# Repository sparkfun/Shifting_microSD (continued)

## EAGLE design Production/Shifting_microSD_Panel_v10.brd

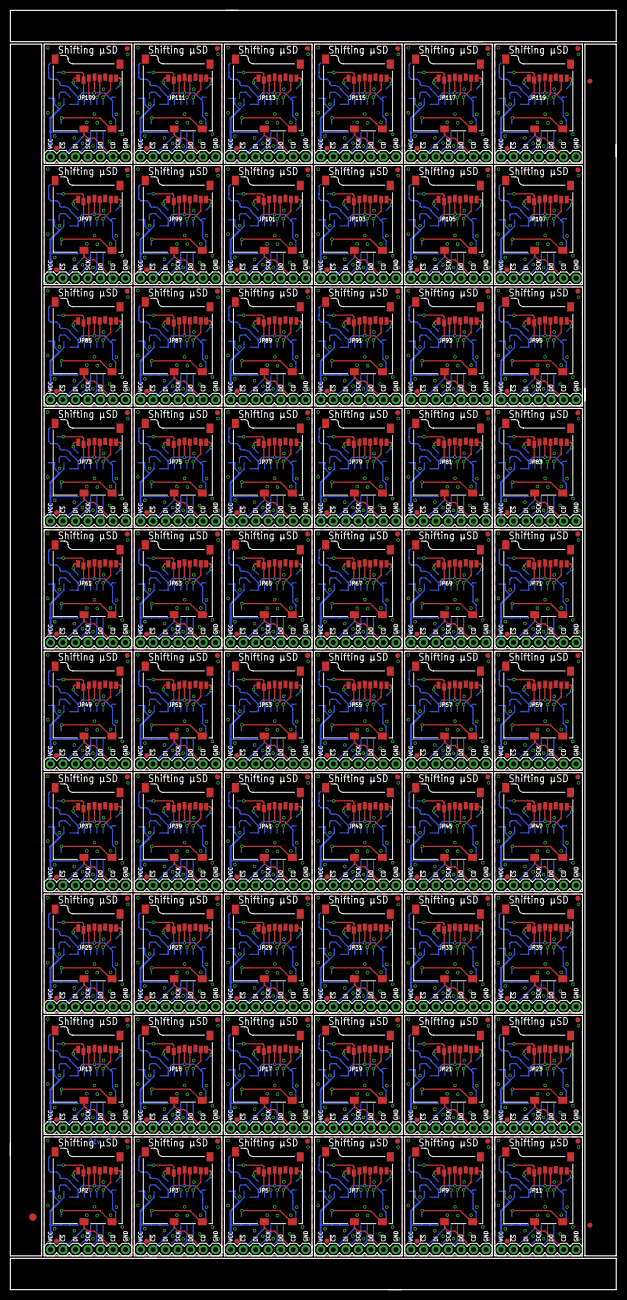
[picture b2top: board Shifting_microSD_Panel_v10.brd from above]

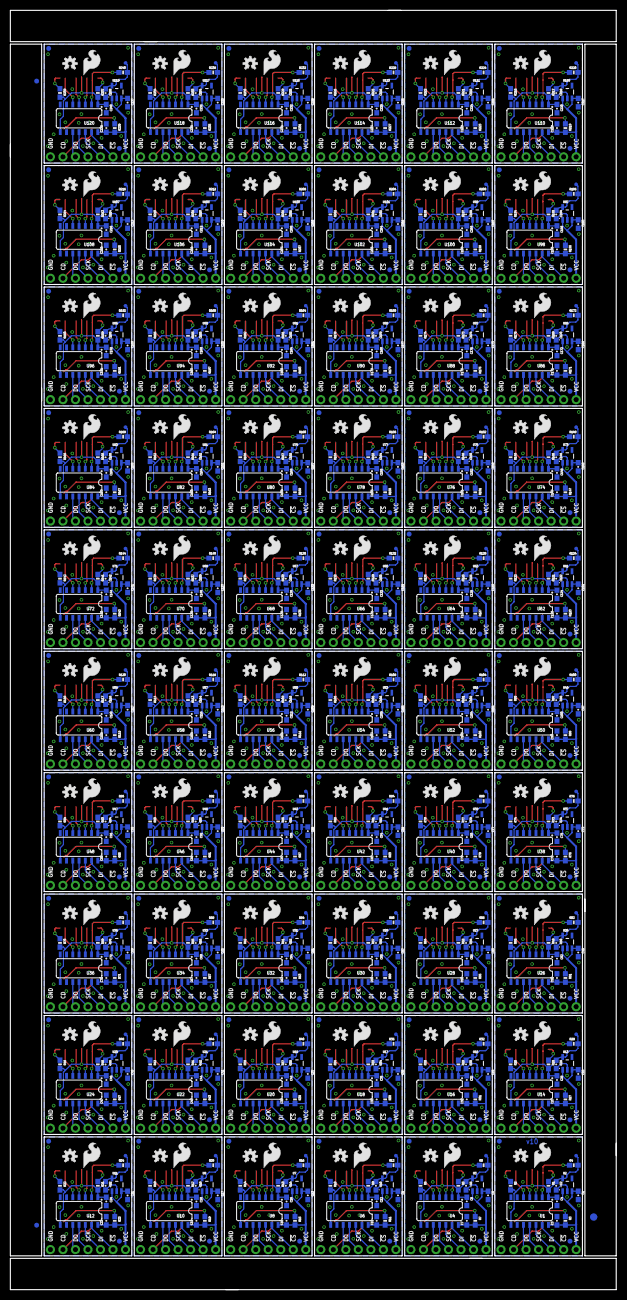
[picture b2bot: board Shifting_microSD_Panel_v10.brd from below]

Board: 2 copper layers, 122.9 x 259.6 mm, 1146 parts (903 on the bottom side), 900 nets.

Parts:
C1, C2, C5, C6, C9, C10, C13, C14, C17, C18, C21, C22, C25, C26, C29, C30, C33, C34, C37, C38, C41, C42, C45, C46, C49, C50, C53, C54, C57, C58, C61, C62, C65, C66, C69, C70, C73, C74, C77, C78, C81, C82, C85, C86, C89, C90, C93, C94, C97, C98, C101, C102, C105, C106, C109, C110, C113, C114, C117, C118, C121, C122, C125, C126, C129, C130, C133, C134, C137, C138, C141, C142, C145, C146, C149, C150, C153, C154, C157, C158, C161, C162, C165, C166, C169, C170, C173, C174, C177, C178, C181, C182, C185, C186, C189, C190, C193, C194, C197, C198, C201, C202, C205, C206, C209, C210, C213, C214, C217, C218, C221, C222, C225, C226, C229, C230, C233, C234, C237, C238: 1.0uF; 0603-CAP
C3, C4, C7, C8, C11, C12, C15, C16, C19, C20, C23, C24, C27, C28, C31, C32, C35, C36, C39, C40, C43, C44, C47, C48, C51, C52, C55, C56, C59, C60, C63, C64, C67, C68, C71, C72, C75, C76, C79, C80, C83, C84, C87, C88, C91, C92, C95, C96, C99, C100, C103, C104, C107, C108, C111, C112, C115, C116, C119, C120, C123, C124, C127, C128, C131, C132, C135, C136, C139, C140, C143, C144, C147, C148, C151, C152, C155, C156, C159, C160, C163, C164, C167, C168, C171, C172, C175, C176, C179, C180, C183, C184, C187, C188, C191, C192, C195, C196, C199, C200, C203, C204, C207, C208, C211, C212, C215, C216, C219, C220, C223, C224, C227, C228, C231, C232, C235, C236, C239, C240: 0.1uF; 0603-CAP
E$1, E$4, E$5, E$6: FIDUCIAL-1X2
E$2, E$3: FIDUCIAL-1.5X3
FID1, FID2, FID3, FID4, FID5, FID6, FID7, FID8, FID9, FID10, FID11, FID12, FID13, FID14, FID15, FID16, FID17, FID18, FID19, FID20, FID21, FID22, FID23, FID24, FID25, FID26, FID27, FID28, FID29, FID30, FID31, FID32, FID33, FID34, FID35, FID36, FID37, FID38, FID39, FID40, FID41, FID42, FID43, FID44, FID45, FID46, FID47, FID48, FID49, FID50, FID51, FID52, FID53, FID54, FID55, FID56, FID57, FID58, FID59, FID60, FID61, FID62, FID63, FID64, FID65, FID66, FID67, FID68, FID69, FID70, FID71, FID72, FID73, FID74, FID75, FID76, FID77, FID78, FID79, FID80, FID81, FID82, FID83, FID84, FID85, FID86, FID87, FID88, FID89, FID90, FID91, FID92, FID93, FID94, FID95, FID96, FID97, FID98, FID99, FID100, FID101, FID102, FID103, FID104, FID105, FID106, FID107, FID108, FID109, FID110, FID111, FID112, FID113, FID114, FID115, FID116, FID117, FID118, FID119, FID120, FID121, FID122, FID123, FID124, FID125, FID126, FID127, FID128, FID129, FID130, FID131, FID132, FID133, FID134, FID135, FID136, FID137, FID138, FID139, FID140, FID141, FID142, FID143, FID144, FID145, FID146, FID147, FID148, FID149, FID150, FID151, FID152, FID153, FID154, FID155, FID156, FID157, FID158, FID159, FID160, FID161, FID162, FID163, FID164, FID165, FID166, FID167, FID168, FID169, FID170, FID171, FID172, FID173, FID174, FID175, FID176, FID177, FID178, FID179, FID180, FID181, FID182, FID183, FID184, FID185, FID186, FID187, FID188, FID189, FID190, FID191, FID192, FID193, FID194, FID195, FID196, FID197, FID198, FID199, FID200, FID201, FID202, FID203, FID204, FID205, FID206, FID207, FID208, FID209, FID210, FID211, FID212, FID213, FID214, FID215, FID216, FID217, FID218, FID219, FID220, FID221, FID222, FID223, FID224, FID225, FID226, FID227, FID228, FID229, FID230, FID231, FID232, FID233, FID234, FID235, FID236, FID237, FID238, FID239, FID240: FIDUCIAL1X2; FIDUCIAL-1X2
JP1, JP4, JP6, JP8, JP10, JP12, JP14, JP16, JP18, JP20, JP22, JP24, JP26, JP28, JP30, JP32, JP34, JP36, JP38, JP40, JP42, JP44, JP46, JP48, JP50, JP52, JP54, JP56, JP58, JP60, JP62, JP64, JP66, JP68, JP70, JP72, JP74, JP76, JP78, JP80, JP82, JP84, JP86, JP88, JP90, JP92, JP94, JP96, JP98, JP100, JP102, JP104, JP106, JP108, JP110, JP112, JP114, JP116, JP118, JP120: 1X07
JP2, JP3, JP5, JP7, JP9, JP11, JP13, JP15, JP17, JP19, JP21, JP23, JP25, JP27, JP29, JP31, JP33, JP35, JP37, JP39, JP41, JP43, JP45, JP47, JP49, JP51, JP53, JP55, JP57, JP59, JP61, JP63, JP65, JP67, JP69, JP71, JP73, JP75, JP77, JP79, JP81, JP83, JP85, JP87, JP89, JP91, JP93, JP95, JP97, JP99, JP101, JP103, JP105, JP107, JP109, JP111, JP113, JP115, JP117, JP119: USD_CONNECTOR; MICRO-SD-SOCKET-PP
LOGO1, LOGO3, LOGO5, LOGO7, LOGO9, LOGO11, LOGO13, LOGO15, LOGO17, LOGO19, LOGO21, LOGO23, LOGO25, LOGO27, LOGO29, LOGO31, LOGO33, LOGO35, LOGO37, LOGO39, LOGO41, LOGO43, LOGO45, LOGO47, LOGO49, LOGO51, LOGO53, LOGO55, LOGO57, LOGO59, LOGO61, LOGO63, LOGO65, LOGO67, LOGO69, LOGO71, LOGO73, LOGO75, LOGO77, LOGO79, LOGO81, LOGO83, LOGO85, LOGO87, LOGO89, LOGO91, LOGO93, LOGO95, LOGO97, LOGO99, LOGO101, LOGO103, LOGO105, LOGO107, LOGO109, LOGO111, LOGO113, LOGO115, LOGO117, LOGO119: SFE_LOGO_FLAME.2_INCH; SFE_LOGO_FLAME_.2
LOGO2, LOGO4, LOGO6, LOGO8, LOGO10, LOGO12, LOGO14, LOGO16, LOGO18, LOGO20, LOGO22, LOGO24, LOGO26, LOGO28, LOGO30, LOGO32, LOGO34, LOGO36, LOGO38, LOGO40, LOGO42, LOGO44, LOGO46, LOGO48, LOGO50, LOGO52, LOGO54, LOGO56, LOGO58, LOGO60, LOGO62, LOGO64, LOGO66, LOGO68, LOGO70, LOGO72, LOGO74, LOGO76, LOGO78, LOGO80, LOGO82, LOGO84, LOGO86, LOGO88, LOGO90, LOGO92, LOGO94, LOGO96, LOGO98, LOGO100, LOGO102, LOGO104, LOGO106, LOGO108, LOGO110, LOGO112, LOGO114, LOGO116, LOGO118, LOGO120: OSHW-LOGOS; OSHW-LOGO-S
R1, R2, R3, R4, R5, R6, R7, R8, R9, R10, R11, R12, R13, R14, R15, R16, R17, R18, R19, R20, R21, R22, R23, R24, R25, R26, R27, R28, R29, R30, R31, R32, R33, R34, R35, R36, R37, R38, R39, R40, R41, R42, R43, R44, R45, R46, R47, R48, R49, R50, R51, R52, R53, R54, R55, R56, R57, R58, R59, R60, R61, R62, R63, R64, R65, R66, R67, R68, R69, R70, R71, R72, R73, R74, R75, R76, R77, R78, R79, R80, R81, R82, R83, R84, R85, R86, R87, R88, R89, R90, R91, R92, R93, R94, R95, R96, R97, R98, R99, R100, R101, R102, R103, R104, R105, R106, R107, R108, R109, R110, R111, R112, R113, R114, R115, R116, R117, R118, R119, R120, R121, R122, R123, R124, R125, R126, R127, R128, R129, R130, R131, R132, R133, R134, R135, R136, R137, R138, R139, R140, R141, R142, R143, R144, R145, R146, R147, R148, R149, R150, R151, R152, R153, R154, R155, R156, R157, R158, R159, R160, R161, R162, R163, R164, R165, R166, R167, R168, R169, R170, R171, R172, R173, R174, R175, R176, R177, R178, R179, R180, R181, R182, R183, R184, R185, R186, R187, R188, R189, R190, R191, R192, R193, R194, R195, R196, R197, R198, R199, R200, R201, R202, R203, R204, R205, R206, R207, R208, R209, R210, R211, R212, R213, R214, R215, R216, R217, R218, R219, R220, R221, R222, R223, R224, R225, R226, R227, R228, R229, R230, R231, R232, R233, R234, R235, R236, R237, R238, R239, R240: 100k; 0603-RES
TP1, TP2, TP3, TP4, TP5, TP6, TP7, TP8, TP9, TP10, TP11, TP12, TP13, TP14, TP15, TP16, TP17, TP18, TP19, TP20, TP21, TP22, TP23, TP24, TP25, TP26, TP27, TP28, TP29, TP30, TP31, TP32, TP33, TP34, TP35, TP36, TP37, TP38, TP39, TP40, TP41, TP42, TP43, TP44, TP45, TP46, TP47, TP48, TP49, TP50, TP51, TP52, TP53, TP54, TP55, TP56, TP57, TP58, TP59, TP60: PAD.03X.03
U1, U4, U6, U8, U10, U12, U14, U16, U18, U20, U22, U24, U26, U28, U30, U32, U34, U36, U38, U40, U42, U44, U46, U48, U50, U52, U54, U56, U58, U60, U62, U64, U66, U68, U70, U72, U74, U76, U78, U80, U82, U84, U86, U88, U90, U92, U94, U96, U98, U100, U102, U104, U106, U108, U110, U112, U114, U116, U118, U120: TXB0104; SO14
U2, U3, U5, U7, U9, U11, U13, U15, U17, U19, U21, U23, U25, U27, U29, U31, U33, U35, U37, U39, U41, U43, U45, U47, U49, U51, U53, U55, U57, U59, U61, U63, U65, U67, U69, U71, U73, U75, U77, U79, U81, U83, U85, U87, U89, U91, U93, U95, U97, U99, U101, U103, U105, U107, U109, U111, U113, U115, U117, U119: 3.3V; SOT23-5

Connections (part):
3V1: C6.1, C8.1, JP3.VCC, R5.2, R6.2, R8.2, TP2.P$1, U3.5, U4.1, U4.8
3V2: C10.1, C12.1, JP5.VCC, R9.2, R10.2, R12.2, TP3.P$1, U5.5, U6.1, U6.8
3V3: C2.1, C4.1, JP2.VCC, R1.2, R2.2, R4.2, TP1.P$1, U1.1, U1.8, U2.5
3V4: C14.1, C16.1, JP7.VCC, R13.2, R14.2, R16.2, TP4.P$1, U7.5, U8.1, U8.8
3V5: C18.1, C20.1, JP9.VCC, R17.2, R18.2, R20.2, TP5.P$1, U9.5, U10.1, U10.8
3V6: C22.1, C24.1, JP11.VCC, R21.2, R22.2, R24.2, TP6.P$1, U11.5, U12.1, U12.8
3V7: C26.1, C28.1, JP13.VCC, R25.2, R26.2, R28.2, TP7.P$1, U13.5, U14.1, U14.8
3V8: C30.1, C32.1, JP15.VCC, R29.2, R30.2, R32.2, TP8.P$1, U15.5, U16.1, U16.8
3V9: C34.1, C36.1, JP17.VCC, R33.2, R34.2, R36.2, TP9.P$1, U17.5, U18.1, U18.8
3V10: C38.1, C40.1, JP19.VCC, R37.2, R38.2, R40.2, TP10.P$1, U19.5, U20.1, U20.8
3V11: C42.1, C44.1, JP21.VCC, R41.2, R42.2, R44.2, TP11.P$1, U21.5, U22.1, U22.8
3V12: C46.1, C48.1, JP23.VCC, R45.2, R46.2, R48.2, TP12.P$1, U23.5, U24.1, U24.8
3V13: C50.1, C52.1, JP25.VCC, R49.2, R50.2, R52.2, TP13.P$1, U25.5, U26.1, U26.8
3V14: C54.1, C56.1, JP27.VCC, R53.2, R54.2, R56.2, TP14.P$1, U27.5, U28.1, U28.8
3V15: C58.1, C60.1, JP29.VCC, R57.2, R58.2, R60.2, TP15.P$1, U29.5, U30.1, U30.8
3V16: C62.1, C64.1, JP31.VCC, R61.2, R62.2, R64.2, TP16.P$1, U31.5, U32.1, U32.8
3V17: C66.1, C68.1, JP33.VCC, R65.2, R66.2, R68.2, TP17.P$1, U33.5, U34.1, U34.8
3V18: C70.1, C72.1, JP35.VCC, R69.2, R70.2, R72.2, TP18.P$1, U35.5, U36.1, U36.8
3V19: C74.1, C76.1, JP37.VCC, R73.2, R74.2, R76.2, TP19.P$1, U37.5, U38.1, U38.8
3V20: C78.1, C80.1, JP39.VCC, R77.2, R78.2, R80.2, TP20.P$1, U39.5, U40.1, U40.8
3V21: C82.1, C84.1, JP41.VCC, R81.2, R82.2, R84.2, TP21.P$1, U41.5, U42.1, U42.8
3V22: C86.1, C88.1, JP43.VCC, R85.2, R86.2, R88.2, TP22.P$1, U43.5, U44.1, U44.8
3V23: C90.1, C92.1, JP45.VCC, R89.2, R90.2, R92.2, TP23.P$1, U45.5, U46.1, U46.8
3V24: C94.1, C96.1, JP47.VCC, R93.2, R94.2, R96.2, TP24.P$1, U47.5, U48.1, U48.8
3V25: C98.1, C100.1, JP49.VCC, R97.2, R98.2, R100.2, TP25.P$1, U49.5, U50.1, U50.8
3V26: C102.1, C104.1, JP51.VCC, R101.2, R102.2, R104.2, TP26.P$1, U51.5, U52.1, U52.8
3V27: C106.1, C108.1, JP53.VCC, R105.2, R106.2, R108.2, TP27.P$1, U53.5, U54.1, U54.8
3V28: C110.1, C112.1, JP55.VCC, R109.2, R110.2, R112.2, TP28.P$1, U55.5, U56.1, U56.8
3V29: C114.1, C116.1, JP57.VCC, R113.2, R114.2, R116.2, TP29.P$1, U57.5, U58.1, U58.8
3V30: C118.1, C120.1, JP59.VCC, R117.2, R118.2, R120.2, TP30.P$1, U59.5, U60.1, U60.8
3V31: C122.1, C124.1, JP61.VCC, R121.2, R122.2, R124.2, TP31.P$1, U61.5, U62.1, U62.8
3V32: C126.1, C128.1, JP63.VCC, R125.2, R126.2, R128.2, TP32.P$1, U63.5, U64.1, U64.8
3V33: C130.1, C132.1, JP65.VCC, R129.2, R130.2, R132.2, TP33.P$1, U65.5, U66.1, U66.8
3V34: C134.1, C136.1, JP67.VCC, R133.2, R134.2, R136.2, TP34.P$1, U67.5, U68.1, U68.8
3V35: C138.1, C140.1, JP69.VCC, R137.2, R138.2, R140.2, TP35.P$1, U69.5, U70.1, U70.8
3V36: C142.1, C144.1, JP71.VCC, R141.2, R142.2, R144.2, TP36.P$1, U71.5, U72.1, U72.8
3V37: C146.1, C148.1, JP73.VCC, R145.2, R146.2, R148.2, TP37.P$1, U73.5, U74.1, U74.8
3V38: C150.1, C152.1, JP75.VCC, R149.2, R150.2, R152.2, TP38.P$1, U75.5, U76.1, U76.8
3V39: C154.1, C156.1, JP77.VCC, R153.2, R154.2, R156.2, TP39.P$1, U77.5, U78.1, U78.8
3V40: C158.1, C160.1, JP79.VCC, R157.2, R158.2, R160.2, TP40.P$1, U79.5, U80.1, U80.8
3V41: C162.1, C164.1, JP81.VCC, R161.2, R162.2, R164.2, TP41.P$1, U81.5, U82.1, U82.8
3V42: C166.1, C168.1, JP83.VCC, R165.2, R166.2, R168.2, TP42.P$1, U83.5, U84.1, U84.8
3V43: C170.1, C172.1, JP85.VCC, R169.2, R170.2, R172.2, TP43.P$1, U85.5, U86.1, U86.8
3V44: C174.1, C176.1, JP87.VCC, R173.2, R174.2, R176.2, TP44.P$1, U87.5, U88.1, U88.8
3V45: C178.1, C180.1, JP89.VCC, R177.2, R178.2, R180.2, TP45.P$1, U89.5, U90.1, U90.8
3V46: C182.1, C184.1, JP91.VCC, R181.2, R182.2, R184.2, TP46.P$1, U91.5, U92.1, U92.8
3V47: C186.1, C188.1, JP93.VCC, R185.2, R186.2, R188.2, TP47.P$1, U93.5, U94.1, U94.8
3V48: C190.1, C192.1, JP95.VCC, R189.2, R190.2, R192.2, TP48.P$1, U95.5, U96.1, U96.8
3V49: C194.1, C196.1, JP97.VCC, R193.2, R194.2, R196.2, TP49.P$1, U97.5, U98.1, U98.8
3V50: C198.1, C200.1, JP99.VCC, R197.2, R198.2, R200.2, TP50.P$1, U99.5, U100.1, U100.8
3V51: C202.1, C204.1, JP101.VCC, R201.2, R202.2, R204.2, TP51.P$1, U101.5, U102.1, U102.8
3V52: C206.1, C208.1, JP103.VCC, R205.2, R206.2, R208.2, TP52.P$1, U103.5, U104.1, U104.8
3V53: C210.1, C212.1, JP105.VCC, R209.2, R210.2, R212.2, TP53.P$1, U105.5, U106.1, U106.8
3V54: C214.1, C216.1, JP107.VCC, R213.2, R214.2, R216.2, TP54.P$1, U107.5, U108.1, U108.8
3V55: C218.1, C220.1, JP109.VCC, R217.2, R218.2, R220.2, TP55.P$1, U109.5, U110.1, U110.8
3V56: C222.1, C224.1, JP111.VCC, R221.2, R222.2, R224.2, TP56.P$1, U111.5, U112.1, U112.8
3V57: C226.1, C228.1, JP113.VCC, R225.2, R226.2, R228.2, TP57.P$1, U113.5, U114.1, U114.8
3V58: C230.1, C232.1, JP115.VCC, R229.2, R230.2, R232.2, TP58.P$1, U115.5, U116.1, U116.8
3V59: C234.1, C236.1, JP117.VCC, R233.2, R234.2, R236.2, TP59.P$1, U117.5, U118.1, U118.8
3V60: C238.1, C240.1, JP119.VCC, R237.2, R238.2, R240.2, TP60.P$1, U119.5, U120.1, U120.8
!CS_3V1: JP3.CS, R8.1, U4.2
!CS_3V2: JP5.CS, R12.1, U6.2
!CS_3V3: JP2.CS, R4.1, U1.2
!CS_3V4: JP7.CS, R16.1, U8.2
!CS_3V5: JP9.CS, R20.1, U10.2
!CS_3V6: JP11.CS, R24.1, U12.2
!CS_3V7: JP13.CS, R28.1, U14.2
!CS_3V8: JP15.CS, R32.1, U16.2
!CS_3V9: JP17.CS, R36.1, U18.2
!CS_3V10: JP19.CS, R40.1, U20.2
!CS_3V11: JP21.CS, R44.1, U22.2
!CS_3V12: JP23.CS, R48.1, U24.2
!CS_3V13: JP25.CS, R52.1, U26.2
!CS_3V14: JP27.CS, R56.1, U28.2
!CS_3V15: JP29.CS, R60.1, U30.2
!CS_3V16: JP31.CS, R64.1, U32.2
!CS_3V17: JP33.CS, R68.1, U34.2
!CS_3V18: JP35.CS, R72.1, U36.2
!CS_3V19: JP37.CS, R76.1, U38.2
!CS_3V20: JP39.CS, R80.1, U40.2
!CS_3V21: JP41.CS, R84.1, U42.2
!CS_3V22: JP43.CS, R88.1, U44.2
!CS_3V23: JP45.CS, R92.1, U46.2
!CS_3V24: JP47.CS, R96.1, U48.2
!CS_3V25: JP49.CS, R100.1, U50.2
!CS_3V26: JP51.CS, R104.1, U52.2
!CS_3V27: JP53.CS, R108.1, U54.2
!CS_3V28: JP55.CS, R112.1, U56.2
!CS_3V29: JP57.CS, R116.1, U58.2
!CS_3V30: JP59.CS, R120.1, U60.2
!CS_3V31: JP61.CS, R124.1, U62.2
!CS_3V32: JP63.CS, R128.1, U64.2
!CS_3V33: JP65.CS, R132.1, U66.2
!CS_3V34: JP67.CS, R136.1, U68.2
!CS_3V35: JP69.CS, R140.1, U70.2
!CS_3V36: JP71.CS, R144.1, U72.2
!CS_3V37: JP73.CS, R148.1, U74.2
!CS_3V38: JP75.CS, R152.1, U76.2
!CS_3V39: JP77.CS, R156.1, U78.2
!CS_3V40: JP79.CS, R160.1, U80.2
!CS_3V41: JP81.CS, R164.1, U82.2
!CS_3V42: JP83.CS, R168.1, U84.2
!CS_3V43: JP85.CS, R172.1, U86.2
!CS_3V44: JP87.CS, R176.1, U88.2
!CS_3V45: JP89.CS, R180.1, U90.2
!CS_3V46: JP91.CS, R184.1, U92.2
!CS_3V47: JP93.CS, R188.1, U94.2
!CS_3V48: JP95.CS, R192.1, U96.2
!CS_3V49: JP97.CS, R196.1, U98.2
!CS_3V50: JP99.CS, R200.1, U100.2
!CS_3V51: JP101.CS, R204.1, U102.2
!CS_3V52: JP103.CS, R208.1, U104.2
!CS_3V53: JP105.CS, R212.1, U106.2
!CS_3V54: JP107.CS, R216.1, U108.2
!CS_3V55: JP109.CS, R220.1, U110.2
!CS_3V56: JP111.CS, R224.1, U112.2
!CS_3V57: JP113.CS, R228.1, U114.2
!CS_3V58: JP115.CS, R232.1, U116.2
!CS_3V59: JP117.CS, R236.1, U118.2
!CS_3V60: JP119.CS, R240.1, U120.2
CD: JP1.2, JP2.CD2
CD1: JP3.CD2, JP4.2
CD2: JP5.CD2, JP6.2
CD3: JP7.CD2, JP8.2
CD4: JP9.CD2, JP10.2
CD5: JP11.CD2, JP12.2
CD6: JP13.CD2, JP14.2
CD7: JP15.CD2, JP16.2
CD8: JP17.CD2, JP18.2
CD9: JP19.CD2, JP20.2
CD10: JP21.CD2, JP22.2
CD11: JP23.CD2, JP24.2
CD12: JP25.CD2, JP26.2
CD13: JP27.CD2, JP28.2
CD14: JP29.CD2, JP30.2
CD15: JP31.CD2, JP32.2
CD16: JP33.CD2, JP34.2
CD17: JP35.CD2, JP36.2
CD18: JP37.CD2, JP38.2
CD19: JP39.CD2, JP40.2
CD20: JP41.CD2, JP42.2
CD21: JP43.CD2, JP44.2
CD22: JP45.CD2, JP46.2
CD23: JP47.CD2, JP48.2
CD24: JP49.CD2, JP50.2
CD25: JP51.CD2, JP52.2
CD26: JP53.CD2, JP54.2
CD27: JP55.CD2, JP56.2
CD28: JP57.CD2, JP58.2
CD29: JP59.CD2, JP60.2
CD30: JP61.CD2, JP62.2
CD31: JP63.CD2, JP64.2
CD32: JP65.CD2, JP66.2
CD33: JP67.CD2, JP68.2
CD34: JP69.CD2, JP70.2
CD35: JP71.CD2, JP72.2
CD36: JP73.CD2, JP74.2
CD37: JP75.CD2, JP76.2
CD38: JP77.CD2, JP78.2
CD39: JP79.CD2, JP80.2
CD40: JP81.CD2, JP82.2
CD41: JP83.CD2, JP84.2
CD42: JP85.CD2, JP86.2
CD43: JP87.CD2, JP88.2
CD44: JP89.CD2, JP90.2
CD45: JP91.CD2, JP92.2
CD46: JP93.CD2, JP94.2
CD47: JP95.CD2, JP96.2
CD48: JP97.CD2, JP98.2
CD49: JP99.CD2, JP100.2
CD50: JP101.CD2, JP102.2
CD51: JP103.CD2, JP104.2
CD52: JP105.CD2, JP106.2
CD53: JP107.CD2, JP108.2
CD54: JP109.CD2, JP110.2
CD55: JP111.CD2, JP112.2
CD56: JP113.CD2, JP114.2
CD57: JP115.CD2, JP116.2
CD58: JP117.CD2, JP118.2
CD59: JP119.CD2, JP120.2
CDSDSD: JP2.CD1, R3.1
CDSDSD1: JP3.CD1, R7.1
CDSDSD2: JP5.CD1, R11.1
CDSDSD3: JP7.CD1, R15.1
CDSDSD4: JP9.CD1, R19.1
CDSDSD5: JP11.CD1, R23.1
CDSDSD6: JP13.CD1, R27.1
CDSDSD7: JP15.CD1, R31.1
CDSDSD8: JP17.CD1, R35.1
CDSDSD9: JP19.CD1, R39.1
CDSDSD10: JP21.CD1, R43.1
CDSDSD11: JP23.CD1, R47.1
CDSDSD12: JP25.CD1, R51.1
CDSDSD13: JP27.CD1, R55.1
CDSDSD14: JP29.CD1, R59.1
CDSDSD15: JP31.CD1, R63.1
CDSDSD16: JP33.CD1, R67.1
CDSDSD17: JP35.CD1, R71.1
CDSDSD18: JP37.CD1, R75.1
CDSDSD19: JP39.CD1, R79.1
CDSDSD20: JP41.CD1, R83.1
CDSDSD21: JP43.CD1, R87.1
CDSDSD22: JP45.CD1, R91.1
CDSDSD23: JP47.CD1, R95.1
CDSDSD24: JP49.CD1, R99.1
CDSDSD25: JP51.CD1, R103.1
CDSDSD26: JP53.CD1, R107.1
CDSDSD27: JP55.CD1, R111.1
CDSDSD28: JP57.CD1, R115.1
CDSDSD29: JP59.CD1, R119.1
CDSDSD30: JP61.CD1, R123.1
CDSDSD31: JP63.CD1, R127.1
CDSDSD32: JP65.CD1, R131.1
CDSDSD33: JP67.CD1, R135.1
CDSDSD34: JP69.CD1, R139.1
CDSDSD35: JP71.CD1, R143.1
CDSDSD36: JP73.CD1, R147.1
CDSDSD37: JP75.CD1, R151.1
CDSDSD38: JP77.CD1, R155.1
CDSDSD39: JP79.CD1, R159.1
CDSDSD40: JP81.CD1, R163.1
CDSDSD41: JP83.CD1, R167.1
CDSDSD42: JP85.CD1, R171.1
CDSDSD43: JP87.CD1, R175.1
CDSDSD44: JP89.CD1, R179.1
CDSDSD45: JP91.CD1, R183.1
CDSDSD46: JP93.CD1, R187.1
CDSDSD47: JP95.CD1, R191.1
CDSDSD48: JP97.CD1, R195.1
CDSDSD49: JP99.CD1, R199.1
CDSDSD50: JP101.CD1, R203.1
CDSDSD51: JP103.CD1, R207.1
CDSDSD52: JP105.CD1, R211.1
CDSDSD53: JP107.CD1, R215.1
CDSDSD54: JP109.CD1, R219.1
CDSDSD55: JP111.CD1, R223.1
CDSDSD56: JP113.CD1, R227.1
CDSDSD57: JP115.CD1, R231.1
CDSDSD58: JP117.CD1, R235.1
CDSDSD59: JP119.CD1, R239.1
DI: JP1.5, U1.12
DI1: JP4.5, U4.12
DI2: JP6.5, U6.12
DI3: JP8.5, U8.12
DI4: JP10.5, U10.12
DI5: JP12.5, U12.12
DI6: JP14.5, U14.12
DI7: JP16.5, U16.12
DI8: JP18.5, U18.12
DI9: JP20.5, U20.12
DI10: JP22.5, U22.12
DI11: JP24.5, U24.12
DI12: JP26.5, U26.12
DI13: JP28.5, U28.12
DI14: JP30.5, U30.12
DI15: JP32.5, U32.12
DI16: JP34.5, U34.12
DI17: JP36.5, U36.12
DI18: JP38.5, U38.12
DI19: JP40.5, U40.12
DI20: JP42.5, U42.12
DI21: JP44.5, U44.12
DI22: JP46.5, U46.12
DI23: JP48.5, U48.12
DI24: JP50.5, U50.12
DI25: JP52.5, U52.12
DI26: JP54.5, U54.12
DI27: JP56.5, U56.12
DI28: JP58.5, U58.12
DI29: JP60.5, U60.12
DI30: JP62.5, U62.12
DI31: JP64.5, U64.12
DI32: JP66.5, U66.12
DI33: JP68.5, U68.12
DI34: JP70.5, U70.12
DI35: JP72.5, U72.12
DI36: JP74.5, U74.12
DI37: JP76.5, U76.12
DI38: JP78.5, U78.12
DI39: JP80.5, U80.12
DI40: JP82.5, U82.12
DI41: JP84.5, U84.12
DI42: JP86.5, U86.12
DI43: JP88.5, U88.12
DI44: JP90.5, U90.12
DI45: JP92.5, U92.12
DI46: JP94.5, U94.12
DI47: JP96.5, U96.12
DI48: JP98.5, U98.12
DI49: JP100.5, U100.12
DI50: JP102.5, U102.12
DI51: JP104.5, U104.12
DI52: JP106.5, U106.12
DI53: JP108.5, U108.12
DI54: JP110.5, U110.12
DI55: JP112.5, U112.12
DI56: JP114.5, U114.12
DI57: JP116.5, U116.12
DI58: JP118.5, U118.12
DI59: JP120.5, U120.12
DI_3V1: JP3.DI, U4.3
DI_3V2: JP5.DI, U6.3
DI_3V3: JP2.DI, U1.3
DI_3V4: JP7.DI, U8.3
DI_3V5: JP9.DI, U10.3
DI_3V6: JP11.DI, U12.3
DI_3V7: JP13.DI, U14.3
DI_3V8: JP15.DI, U16.3
DI_3V9: JP17.DI, U18.3
DI_3V10: JP19.DI, U20.3
DI_3V11: JP21.DI, U22.3
DI_3V12: JP23.DI, U24.3
DI_3V13: JP25.DI, U26.3
DI_3V14: JP27.DI, U28.3
DI_3V15: JP29.DI, U30.3
DI_3V16: JP31.DI, U32.3
DI_3V17: JP33.DI, U34.3
DI_3V18: JP35.DI, U36.3
DI_3V19: JP37.DI, U38.3
DI_3V20: JP39.DI, U40.3
DI_3V21: JP41.DI, U42.3
DI_3V22: JP43.DI, U44.3
DI_3V23: JP45.DI, U46.3
DI_3V24: JP47.DI, U48.3
DI_3V25: JP49.DI, U50.3
DI_3V26: JP51.DI, U52.3
DI_3V27: JP53.DI, U54.3
DI_3V28: JP55.DI, U56.3
DI_3V29: JP57.DI, U58.3
DI_3V30: JP59.DI, U60.3
DI_3V31: JP61.DI, U62.3
DI_3V32: JP63.DI, U64.3
DI_3V33: JP65.DI, U66.3
DI_3V34: JP67.DI, U68.3
DI_3V35: JP69.DI, U70.3
DI_3V36: JP71.DI, U72.3
DI_3V37: JP73.DI, U74.3
DI_3V38: JP75.DI, U76.3
DI_3V39: JP77.DI, U78.3
DI_3V40: JP79.DI, U80.3
DI_3V41: JP81.DI, U82.3
DI_3V42: JP83.DI, U84.3
DI_3V43: JP85.DI, U86.3
DI_3V44: JP87.DI, U88.3
DI_3V45: JP89.DI, U90.3
DI_3V46: JP91.DI, U92.3
DI_3V47: JP93.DI, U94.3
DI_3V48: JP95.DI, U96.3
DI_3V49: JP97.DI, U98.3
DI_3V50: JP99.DI, U100.3
DI_3V51: JP101.DI, U102.3
DI_3V52: JP103.DI, U104.3
DI_3V53: JP105.DI, U106.3
DI_3V54: JP107.DI, U108.3
DI_3V55: JP109.DI, U110.3
DI_3V56: JP111.DI, U112.3
DI_3V57: JP113.DI, U114.3
DI_3V58: JP115.DI, U116.3
DI_3V59: JP117.DI, U118.3
DI_3V60: JP119.DI, U120.3
DO: JP1.3, U1.10
DO1: JP4.3, U4.10
DO2: JP6.3, U6.10
DO3: JP8.3, U8.10
DO4: JP10.3, U10.10
DO5: JP12.3, U12.10
DO6: JP14.3, U14.10
DO7: JP16.3, U16.10
DO8: JP18.3, U18.10
DO9: JP20.3, U20.10
DO10: JP22.3, U22.10
DO11: JP24.3, U24.10
DO12: JP26.3, U26.10
DO13: JP28.3, U28.10
DO14: JP30.3, U30.10
DO15: JP32.3, U32.10
DO16: JP34.3, U34.10
DO17: JP36.3, U36.10
DO18: JP38.3, U38.10
DO19: JP40.3, U40.10
DO20: JP42.3, U42.10
DO21: JP44.3, U44.10
DO22: JP46.3, U46.10
DO23: JP48.3, U48.10
DO24: JP50.3, U50.10
DO25: JP52.3, U52.10
DO26: JP54.3, U54.10
DO27: JP56.3, U56.10
DO28: JP58.3, U58.10
DO29: JP60.3, U60.10
DO30: JP62.3, U62.10
DO31: JP64.3, U64.10
DO32: JP66.3, U66.10
DO33: JP68.3, U68.10
DO34: JP70.3, U70.10
DO35: JP72.3, U72.10
DO36: JP74.3, U74.10
DO37: JP76.3, U76.10
DO38: JP78.3, U78.10
DO39: JP80.3, U80.10
DO40: JP82.3, U82.10
DO41: JP84.3, U84.10
DO42: JP86.3, U86.10
DO43: JP88.3, U88.10
DO44: JP90.3, U90.10
DO45: JP92.3, U92.10
DO46: JP94.3, U94.10
DO47: JP96.3, U96.10
DO48: JP98.3, U98.10
DO49: JP100.3, U100.10
DO50: JP102.3, U102.10
DO51: JP104.3, U104.10
DO52: JP106.3, U106.10
DO53: JP108.3, U108.10
DO54: JP110.3, U110.10
DO55: JP112.3, U112.10
DO56: JP114.3, U114.10
DO57: JP116.3, U116.10
DO58: JP118.3, U118.10
DO59: JP120.3, U120.10
DO_3V1: JP3.DO, U4.5
DO_3V2: JP5.DO, U6.5
DO_3V3: JP2.DO, U1.5
DO_3V4: JP7.DO, U8.5
DO_3V5: JP9.DO, U10.5
DO_3V6: JP11.DO, U12.5
DO_3V7: JP13.DO, U14.5
DO_3V8: JP15.DO, U16.5
DO_3V9: JP17.DO, U18.5
DO_3V10: JP19.DO, U20.5
DO_3V11: JP21.DO, U22.5
DO_3V12: JP23.DO, U24.5
DO_3V13: JP25.DO, U26.5
DO_3V14: JP27.DO, U28.5
DO_3V15: JP29.DO, U30.5
DO_3V16: JP31.DO, U32.5
DO_3V17: JP33.DO, U34.5
DO_3V18: JP35.DO, U36.5
DO_3V19: JP37.DO, U38.5
DO_3V20: JP39.DO, U40.5
DO_3V21: JP41.DO, U42.5
DO_3V22: JP43.DO, U44.5
DO_3V23: JP45.DO, U46.5
DO_3V24: JP47.DO, U48.5
DO_3V25: JP49.DO, U50.5
DO_3V26: JP51.DO, U52.5
DO_3V27: JP53.DO, U54.5
DO_3V28: JP55.DO, U56.5
DO_3V29: JP57.DO, U58.5
DO_3V30: JP59.DO, U60.5
DO_3V31: JP61.DO, U62.5
DO_3V32: JP63.DO, U64.5
DO_3V33: JP65.DO, U66.5
DO_3V34: JP67.DO, U68.5
DO_3V35: JP69.DO, U70.5
DO_3V36: JP71.DO, U72.5
DO_3V37: JP73.DO, U74.5
DO_3V38: JP75.DO, U76.5
DO_3V39: JP77.DO, U78.5
DO_3V40: JP79.DO, U80.5
DO_3V41: JP81.DO, U82.5
DO_3V42: JP83.DO, U84.5
DO_3V43: JP85.DO, U86.5
DO_3V44: JP87.DO, U88.5
DO_3V45: JP89.DO, U90.5
DO_3V46: JP91.DO, U92.5
DO_3V47: JP93.DO, U94.5
DO_3V48: JP95.DO, U96.5
DO_3V49: JP97.DO, U98.5
DO_3V50: JP99.DO, U100.5
DO_3V51: JP101.DO, U102.5
DO_3V52: JP103.DO, U104.5
DO_3V53: JP105.DO, U106.5
DO_3V54: JP107.DO, U108.5
DO_3V55: JP109.DO, U110.5
DO_3V56: JP111.DO, U112.5
DO_3V57: JP113.DO, U114.5
DO_3V58: JP115.DO, U116.5
DO_3V59: JP117.DO, U118.5
DO_3V60: JP119.DO, U120.5
GND: C1.2, C2.2, C3.2, C4.2, JP1.1, JP2.GND, JP2.GND1, JP2.GND3, U1.7, U2.2
GND1: C5.2, C6.2, C7.2, C8.2, JP3.GND, JP3.GND1, JP3.GND3, JP4.1, U3.2, U4.7
GND2: C9.2, C10.2, C11.2, C12.2, JP5.GND, JP5.GND1, JP5.GND3, JP6.1, U5.2, U6.7
GND3: C13.2, C14.2, C15.2, C16.2, JP7.GND, JP7.GND1, JP7.GND3, JP8.1, U7.2, U8.7
GND4: C17.2, C18.2, C19.2, C20.2, JP9.GND, JP9.GND1, JP9.GND3, JP10.1, U9.2, U10.7
GND5: C21.2, C22.2, C23.2, C24.2, JP11.GND, JP11.GND1, JP11.GND3, JP12.1, U11.2, U12.7
GND6: C25.2, C26.2, C27.2, C28.2, JP13.GND, JP13.GND1, JP13.GND3, JP14.1, U13.2, U14.7
GND7: C29.2, C30.2, C31.2, C32.2, JP15.GND, JP15.GND1, JP15.GND3, JP16.1, U15.2, U16.7
GND8: C33.2, C34.2, C35.2, C36.2, JP17.GND, JP17.GND1, JP17.GND3, JP18.1, U17.2, U18.7
GND9: C37.2, C38.2, C39.2, C40.2, JP19.GND, JP19.GND1, JP19.GND3, JP20.1, U19.2, U20.7
GND10: C41.2, C42.2, C43.2, C44.2, JP21.GND, JP21.GND1, JP21.GND3, JP22.1, U21.2, U22.7
GND11: C45.2, C46.2, C47.2, C48.2, JP23.GND, JP23.GND1, JP23.GND3, JP24.1, U23.2, U24.7
GND12: C49.2, C50.2, C51.2, C52.2, JP25.GND, JP25.GND1, JP25.GND3, JP26.1, U25.2, U26.7
GND13: C53.2, C54.2, C55.2, C56.2, JP27.GND, JP27.GND1, JP27.GND3, JP28.1, U27.2, U28.7
GND14: C57.2, C58.2, C59.2, C60.2, JP29.GND, JP29.GND1, JP29.GND3, JP30.1, U29.2, U30.7
GND15: C61.2, C62.2, C63.2, C64.2, JP31.GND, JP31.GND1, JP31.GND3, JP32.1, U31.2, U32.7
GND16: C65.2, C66.2, C67.2, C68.2, JP33.GND, JP33.GND1, JP33.GND3, JP34.1, U33.2, U34.7
GND17: C69.2, C70.2, C71.2, C72.2, JP35.GND, JP35.GND1, JP35.GND3, JP36.1, U35.2, U36.7
GND18: C73.2, C74.2, C75.2, C76.2, JP37.GND, JP37.GND1, JP37.GND3, JP38.1, U37.2, U38.7
GND19: C77.2, C78.2, C79.2, C80.2, JP39.GND, JP39.GND1, JP39.GND3, JP40.1, U39.2, U40.7
GND20: C81.2, C82.2, C83.2, C84.2, JP41.GND, JP41.GND1, JP41.GND3, JP42.1, U41.2, U42.7
GND21: C85.2, C86.2, C87.2, C88.2, JP43.GND, JP43.GND1, JP43.GND3, JP44.1, U43.2, U44.7
GND22: C89.2, C90.2, C91.2, C92.2, JP45.GND, JP45.GND1, JP45.GND3, JP46.1, U45.2, U46.7
GND23: C93.2, C94.2, C95.2, C96.2, JP47.GND, JP47.GND1, JP47.GND3, JP48.1, U47.2, U48.7
GND24: C97.2, C98.2, C99.2, C100.2, JP49.GND, JP49.GND1, JP49.GND3, JP50.1, U49.2, U50.7
GND25: C101.2, C102.2, C103.2, C104.2, JP51.GND, JP51.GND1, JP51.GND3, JP52.1, U51.2, U52.7
GND26: C105.2, C106.2, C107.2, C108.2, JP53.GND, JP53.GND1, JP53.GND3, JP54.1, U53.2, U54.7
GND27: C109.2, C110.2, C111.2, C112.2, JP55.GND, JP55.GND1, JP55.GND3, JP56.1, U55.2, U56.7
GND28: C113.2, C114.2, C115.2, C116.2, JP57.GND, JP57.GND1, JP57.GND3, JP58.1, U57.2, U58.7
GND29: C117.2, C118.2, C119.2, C120.2, JP59.GND, JP59.GND1, JP59.GND3, JP60.1, U59.2, U60.7
GND30: C121.2, C122.2, C123.2, C124.2, JP61.GND, JP61.GND1, JP61.GND3, JP62.1, U61.2, U62.7
GND31: C125.2, C126.2, C127.2, C128.2, JP63.GND, JP63.GND1, JP63.GND3, JP64.1, U63.2, U64.7
GND32: C129.2, C130.2, C131.2, C132.2, JP65.GND, JP65.GND1, JP65.GND3, JP66.1, U65.2, U66.7
GND33: C133.2, C134.2, C135.2, C136.2, JP67.GND, JP67.GND1, JP67.GND3, JP68.1, U67.2, U68.7
GND34: C137.2, C138.2, C139.2, C140.2, JP69.GND, JP69.GND1, JP69.GND3, JP70.1, U69.2, U70.7
GND35: C141.2, C142.2, C143.2, C144.2, JP71.GND, JP71.GND1, JP71.GND3, JP72.1, U71.2, U72.7
GND36: C145.2, C146.2, C147.2, C148.2, JP73.GND, JP73.GND1, JP73.GND3, JP74.1, U73.2, U74.7
GND37: C149.2, C150.2, C151.2, C152.2, JP75.GND, JP75.GND1, JP75.GND3, JP76.1, U75.2, U76.7
GND38: C153.2, C154.2, C155.2, C156.2, JP77.GND, JP77.GND1, JP77.GND3, JP78.1, U77.2, U78.7
GND39: C157.2, C158.2, C159.2, C160.2, JP79.GND, JP79.GND1, JP79.GND3, JP80.1, U79.2, U80.7
GND40: C161.2, C162.2, C163.2, C164.2, JP81.GND, JP81.GND1, JP81.GND3, JP82.1, U81.2, U82.7
GND41: C165.2, C166.2, C167.2, C168.2, JP83.GND, JP83.GND1, JP83.GND3, JP84.1, U83.2, U84.7
GND42: C169.2, C170.2, C171.2, C172.2, JP85.GND, JP85.GND1, JP85.GND3, JP86.1, U85.2, U86.7
GND43: C173.2, C174.2, C175.2, C176.2, JP87.GND, JP87.GND1, JP87.GND3, JP88.1, U87.2, U88.7
GND44: C177.2, C178.2, C179.2, C180.2, JP89.GND, JP89.GND1, JP89.GND3, JP90.1, U89.2, U90.7
GND45: C181.2, C182.2, C183.2, C184.2, JP91.GND, JP91.GND1, JP91.GND3, JP92.1, U91.2, U92.7
GND46: C185.2, C186.2, C187.2, C188.2, JP93.GND, JP93.GND1, JP93.GND3, JP94.1, U93.2, U94.7
GND47: C189.2, C190.2, C191.2, C192.2, JP95.GND, JP95.GND1, JP95.GND3, JP96.1, U95.2, U96.7
GND48: C193.2, C194.2, C195.2, C196.2, JP97.GND, JP97.GND1, JP97.GND3, JP98.1, U97.2, U98.7
GND49: C197.2, C198.2, C199.2, C200.2, JP99.GND, JP99.GND1, JP99.GND3, JP100.1, U99.2, U100.7
GND50: C201.2, C202.2, C203.2, C204.2, JP101.GND, JP101.GND1, JP101.GND3, JP102.1, U101.2, U102.7
GND51: C205.2, C206.2, C207.2, C208.2, JP103.GND, JP103.GND1, JP103.GND3, JP104.1, U103.2, U104.7
GND52: C209.2, C210.2, C211.2, C212.2, JP105.GND, JP105.GND1, JP105.GND3, JP106.1, U105.2, U106.7
GND53: C213.2, C214.2, C215.2, C216.2, JP107.GND, JP107.GND1, JP107.GND3, JP108.1, U107.2, U108.7
GND54: C217.2, C218.2, C219.2, C220.2, JP109.GND, JP109.GND1, JP109.GND3, JP110.1, U109.2, U110.7
GND55: C221.2, C222.2, C223.2, C224.2, JP111.GND, JP111.GND1, JP111.GND3, JP112.1, U111.2, U112.7
GND56: C225.2, C226.2, C227.2, C228.2, JP113.GND, JP113.GND1, JP113.GND3, JP114.1, U113.2, U114.7
GND57: C229.2, C230.2, C231.2, C232.2, JP115.GND, JP115.GND1, JP115.GND3, JP116.1, U115.2, U116.7
GND58: C233.2, C234.2, C235.2, C236.2, JP117.GND, JP117.GND1, JP117.GND3, JP118.1, U117.2, U118.7
GND59: C237.2, C238.2, C239.2, C240.2, JP119.GND, JP119.GND1, JP119.GND3, JP120.1, U119.2, U120.7
unnamed: JP1.6, U1.13
unnamed: JP4.6, U4.13
unnamed: JP1.4, U1.11
unnamed: JP4.4, U4.11
unnamed: JP6.6, U6.13
unnamed: JP6.4, U6.11
unnamed: JP8.6, U8.13
unnamed: JP8.4, U8.11
unnamed: JP10.6, U10.13
unnamed: JP10.4, U10.11
unnamed: JP12.6, U12.13
unnamed: JP12.4, U12.11
unnamed: JP14.6, U14.13
unnamed: JP14.4, U14.11
unnamed: JP16.6, U16.13
unnamed: JP16.4, U16.11
unnamed: JP18.6, U18.13
unnamed: JP18.4, U18.11
unnamed: JP20.6, U20.13
unnamed: JP20.4, U20.11
unnamed: JP22.6, U22.13
unnamed: JP22.4, U22.11
unnamed: JP24.6, U24.13
unnamed: JP24.4, U24.11
unnamed: JP26.6, U26.13
unnamed: JP26.4, U26.11
unnamed: JP28.6, U28.13
unnamed: JP28.4, U28.11
unnamed: JP30.6, U30.13
unnamed: JP30.4, U30.11
unnamed: JP32.6, U32.13
unnamed: JP32.4, U32.11
unnamed: JP34.6, U34.13
unnamed: JP34.4, U34.11
unnamed: JP36.6, U36.13
unnamed: JP36.4, U36.11
unnamed: JP38.6, U38.13
unnamed: JP38.4, U38.11
unnamed: JP40.6, U40.13
unnamed: JP40.4, U40.11
unnamed: JP42.6, U42.13
unnamed: JP42.4, U42.11
unnamed: JP44.6, U44.13
unnamed: JP44.4, U44.11
unnamed: JP46.6, U46.13
unnamed: JP46.4, U46.11
unnamed: JP48.6, U48.13
unnamed: JP48.4, U48.11
unnamed: JP50.6, U50.13
unnamed: JP50.4, U50.11
unnamed: JP52.6, U52.13
unnamed: JP52.4, U52.11
unnamed: JP54.6, U54.13
unnamed: JP54.4, U54.11
unnamed: JP56.6, U56.13
unnamed: JP56.4, U56.11
unnamed: JP58.6, U58.13
unnamed: JP58.4, U58.11
unnamed: JP60.6, U60.13
unnamed: JP60.4, U60.11
unnamed: JP62.6, U62.13
unnamed: JP62.4, U62.11
unnamed: JP64.6, U64.13
unnamed: JP64.4, U64.11
unnamed: JP66.6, U66.13
unnamed: JP66.4, U66.11
unnamed: JP68.6, U68.13
unnamed: JP68.4, U68.11
unnamed: JP70.6, U70.13
unnamed: JP70.4, U70.11
unnamed: JP72.6, U72.13
unnamed: JP72.4, U72.11
unnamed: JP74.6, U74.13
unnamed: JP74.4, U74.11
unnamed: JP76.6, U76.13
unnamed: JP76.4, U76.11
unnamed: JP78.6, U78.13
unnamed: JP78.4, U78.11
unnamed: JP80.6, U80.13
unnamed: JP80.4, U80.11
unnamed: JP82.6, U82.13
unnamed: JP82.4, U82.11
unnamed: JP84.6, U84.13
unnamed: JP84.4, U84.11
unnamed: JP86.6, U86.13
unnamed: JP86.4, U86.11
unnamed: JP88.6, U88.13
unnamed: JP88.4, U88.11
unnamed: JP90.6, U90.13
unnamed: JP90.4, U90.11
unnamed: JP92.6, U92.13
unnamed: JP92.4, U92.11
unnamed: JP94.6, U94.13
unnamed: JP94.4, U94.11
unnamed: JP96.6, U96.13
unnamed: JP96.4, U96.11
unnamed: JP98.6, U98.13
unnamed: JP98.4, U98.11
unnamed: JP100.6, U100.13
unnamed: JP100.4, U100.11
unnamed: JP102.6, U102.13
unnamed: JP102.4, U102.11
unnamed: JP104.6, U104.13
unnamed: JP104.4, U104.11
unnamed: JP106.6, U106.13
unnamed: JP106.4, U106.11
unnamed: JP108.6, U108.13
unnamed: JP108.4, U108.11
unnamed: JP110.6, U110.13
unnamed: JP110.4, U110.11
unnamed: JP112.6, U112.13
unnamed: JP112.4, U112.11
unnamed: JP114.6, U114.13
unnamed: JP114.4, U114.11
unnamed: JP116.6, U116.13
unnamed: JP116.4, U116.11
unnamed: JP118.6, U118.13
unnamed: JP118.4, U118.11
unnamed: JP120.6, U120.13
unnamed: JP120.4, U120.11
RSV@1: JP2.RSV1, R1.1
RSV@2: JP2.RSV2, R2.1
RSV@3: JP3.RSV1, R5.1
RSV@4: JP3.RSV2, R6.1
RSV@5: JP5.RSV1, R9.1
RSV@6: JP5.RSV2, R10.1
RSV@7: JP7.RSV1, R13.1
RSV@8: JP7.RSV2, R14.1
RSV@9: JP9.RSV1, R17.1
RSV@10: JP9.RSV2, R18.1
RSV@11: JP11.RSV1, R21.1
RSV@12: JP11.RSV2, R22.1
RSV@13: JP13.RSV1, R25.1
RSV@14: JP13.RSV2, R26.1
RSV@15: JP15.RSV1, R29.1
RSV@16: JP15.RSV2, R30.1
RSV@17: JP17.RSV1, R33.1
RSV@18: JP17.RSV2, R34.1
RSV@19: JP19.RSV1, R37.1
RSV@20: JP19.RSV2, R38.1
RSV@21: JP21.RSV1, R41.1
RSV@22: JP21.RSV2, R42.1
RSV@23: JP23.RSV1, R45.1
RSV@24: JP23.RSV2, R46.1
RSV@25: JP25.RSV1, R49.1
RSV@26: JP25.RSV2, R50.1
RSV@27: JP27.RSV1, R53.1
RSV@28: JP27.RSV2, R54.1
RSV@29: JP29.RSV1, R57.1
RSV@30: JP29.RSV2, R58.1
RSV@31: JP31.RSV1, R61.1
RSV@32: JP31.RSV2, R62.1
RSV@33: JP33.RSV1, R65.1
RSV@34: JP33.RSV2, R66.1
RSV@35: JP35.RSV1, R69.1
RSV@36: JP35.RSV2, R70.1
RSV@37: JP37.RSV1, R73.1
RSV@38: JP37.RSV2, R74.1
RSV@39: JP39.RSV1, R77.1
RSV@40: JP39.RSV2, R78.1
RSV@41: JP41.RSV1, R81.1
RSV@42: JP41.RSV2, R82.1
RSV@43: JP43.RSV1, R85.1
RSV@44: JP43.RSV2, R86.1
RSV@45: JP45.RSV1, R89.1
RSV@46: JP45.RSV2, R90.1
RSV@47: JP47.RSV1, R93.1
RSV@48: JP47.RSV2, R94.1
RSV@49: JP49.RSV1, R97.1
RSV@50: JP49.RSV2, R98.1
RSV@51: JP51.RSV1, R101.1
RSV@52: JP51.RSV2, R102.1
RSV@53: JP53.RSV1, R105.1
RSV@54: JP53.RSV2, R106.1
RSV@55: JP55.RSV1, R109.1
RSV@56: JP55.RSV2, R110.1
RSV@57: JP57.RSV1, R113.1
RSV@58: JP57.RSV2, R114.1
RSV@59: JP59.RSV1, R117.1
RSV@60: JP59.RSV2, R118.1
RSV@61: JP61.RSV1, R121.1
RSV@62: JP61.RSV2, R122.1
RSV@63: JP63.RSV1, R125.1
RSV@64: JP63.RSV2, R126.1
RSV@65: JP65.RSV1, R129.1
RSV@66: JP65.RSV2, R130.1
RSV@67: JP67.RSV1, R133.1
RSV@68: JP67.RSV2, R134.1
RSV@69: JP69.RSV1, R137.1
RSV@70: JP69.RSV2, R138.1
RSV@71: JP71.RSV1, R141.1
RSV@72: JP71.RSV2, R142.1
RSV@73: JP73.RSV1, R145.1
RSV@74: JP73.RSV2, R146.1
RSV@75: JP75.RSV1, R149.1
RSV@76: JP75.RSV2, R150.1
RSV@77: JP77.RSV1, R153.1
RSV@78: JP77.RSV2, R154.1
RSV@79: JP79.RSV1, R157.1
RSV@80: JP79.RSV2, R158.1
RSV@81: JP81.RSV1, R161.1
RSV@82: JP81.RSV2, R162.1
RSV@83: JP83.RSV1, R165.1
RSV@84: JP83.RSV2, R166.1
RSV@85: JP85.RSV1, R169.1
RSV@86: JP85.RSV2, R170.1
RSV@87: JP87.RSV1, R173.1
RSV@88: JP87.RSV2, R174.1
RSV@89: JP89.RSV1, R177.1
RSV@90: JP89.RSV2, R178.1
RSV@91: JP91.RSV1, R181.1
RSV@92: JP91.RSV2, R182.1
RSV@93: JP93.RSV1, R185.1
RSV@94: JP93.RSV2, R186.1
RSV@95: JP95.RSV1, R189.1
RSV@96: JP95.RSV2, R190.1
RSV@97: JP97.RSV1, R193.1
RSV@98: JP97.RSV2, R194.1
RSV@99: JP99.RSV1, R197.1
RSV@100: JP99.RSV2, R198.1
RSV@101: JP101.RSV1, R201.1
RSV@102: JP101.RSV2, R202.1
RSV@103: JP103.RSV1, R205.1
RSV@104: JP103.RSV2, R206.1
RSV@105: JP105.RSV1, R209.1
RSV@106: JP105.RSV2, R210.1
RSV@107: JP107.RSV1, R213.1
RSV@108: JP107.RSV2, R214.1
RSV@109: JP109.RSV1, R217.1
RSV@110: JP109.RSV2, R218.1
RSV@111: JP111.RSV1, R221.1
RSV@112: JP111.RSV2, R222.1
RSV@113: JP113.RSV1, R225.1
RSV@114: JP113.RSV2, R226.1
RSV@115: JP115.RSV1, R229.1
RSV@116: JP115.RSV2, R230.1
RSV@117: JP117.RSV1, R233.1
RSV@118: JP117.RSV2, R234.1
RSV@119: JP119.RSV1, R237.1
RSV@120: JP119.RSV2, R238.1
SCK_3V1: JP3.SCLK, U4.4
SCK_3V2: JP5.SCLK, U6.4
SCK_3V3: JP2.SCLK, U1.4
SCK_3V4: JP7.SCLK, U8.4
SCK_3V5: JP9.SCLK, U10.4
SCK_3V6: JP11.SCLK, U12.4
SCK_3V7: JP13.SCLK, U14.4
SCK_3V8: JP15.SCLK, U16.4
SCK_3V9: JP17.SCLK, U18.4
SCK_3V10: JP19.SCLK, U20.4
SCK_3V11: JP21.SCLK, U22.4
SCK_3V12: JP23.SCLK, U24.4
SCK_3V13: JP25.SCLK, U26.4
SCK_3V14: JP27.SCLK, U28.4
SCK_3V15: JP29.SCLK, U30.4
SCK_3V16: JP31.SCLK, U32.4
SCK_3V17: JP33.SCLK, U34.4
SCK_3V18: JP35.SCLK, U36.4
SCK_3V19: JP37.SCLK, U38.4
SCK_3V20: JP39.SCLK, U40.4
SCK_3V21: JP41.SCLK, U42.4
SCK_3V22: JP43.SCLK, U44.4
SCK_3V23: JP45.SCLK, U46.4
SCK_3V24: JP47.SCLK, U48.4
SCK_3V25: JP49.SCLK, U50.4
SCK_3V26: JP51.SCLK, U52.4
SCK_3V27: JP53.SCLK, U54.4
SCK_3V28: JP55.SCLK, U56.4
SCK_3V29: JP57.SCLK, U58.4
SCK_3V30: JP59.SCLK, U60.4
SCK_3V31: JP61.SCLK, U62.4
SCK_3V32: JP63.SCLK, U64.4
SCK_3V33: JP65.SCLK, U66.4
SCK_3V34: JP67.SCLK, U68.4
SCK_3V35: JP69.SCLK, U70.4
SCK_3V36: JP71.SCLK, U72.4
SCK_3V37: JP73.SCLK, U74.4
SCK_3V38: JP75.SCLK, U76.4
SCK_3V39: JP77.SCLK, U78.4
SCK_3V40: JP79.SCLK, U80.4
SCK_3V41: JP81.SCLK, U82.4
SCK_3V42: JP83.SCLK, U84.4
SCK_3V43: JP85.SCLK, U86.4
SCK_3V44: JP87.SCLK, U88.4
SCK_3V45: JP89.SCLK, U90.4
SCK_3V46: JP91.SCLK, U92.4
SCK_3V47: JP93.SCLK, U94.4
SCK_3V48: JP95.SCLK, U96.4
SCK_3V49: JP97.SCLK, U98.4
SCK_3V50: JP99.SCLK, U100.4
SCK_3V51: JP101.SCLK, U102.4
SCK_3V52: JP103.SCLK, U104.4
SCK_3V53: JP105.SCLK, U106.4
SCK_3V54: JP107.SCLK, U108.4
SCK_3V55: JP109.SCLK, U110.4
SCK_3V56: JP111.SCLK, U112.4
SCK_3V57: JP113.SCLK, U114.4
SCK_3V58: JP115.SCLK, U116.4
SCK_3V59: JP117.SCLK, U118.4
SCK_3V60: JP119.SCLK, U120.4
VDD_IO: C1.1, C3.1, JP1.7, R3.2, U1.14, U2.1, U2.3
VDD_IO1: C5.1, C7.1, JP4.7, R7.2, U3.1, U3.3, U4.14
VDD_IO2: C9.1, C11.1, JP6.7, R11.2, U5.1, U5.3, U6.14
VDD_IO3: C13.1, C15.1, JP8.7, R15.2, U7.1, U7.3, U8.14
VDD_IO4: C17.1, C19.1, JP10.7, R19.2, U9.1, U9.3, U10.14
VDD_IO5: C21.1, C23.1, JP12.7, R23.2, U11.1, U11.3, U12.14
VDD_IO6: C25.1, C27.1, JP14.7, R27.2, U13.1, U13.3, U14.14
VDD_IO7: C29.1, C31.1, JP16.7, R31.2, U15.1, U15.3, U16.14
VDD_IO8: C33.1, C35.1, JP18.7, R35.2, U17.1, U17.3, U18.14
VDD_IO9: C37.1, C39.1, JP20.7, R39.2, U19.1, U19.3, U20.14
VDD_IO10: C41.1, C43.1, JP22.7, R43.2, U21.1, U21.3, U22.14
VDD_IO11: C45.1, C47.1, JP24.7, R47.2, U23.1, U23.3, U24.14
VDD_IO12: C49.1, C51.1, JP26.7, R51.2, U25.1, U25.3, U26.14
VDD_IO13: C53.1, C55.1, JP28.7, R55.2, U27.1, U27.3, U28.14
VDD_IO14: C57.1, C59.1, JP30.7, R59.2, U29.1, U29.3, U30.14
VDD_IO15: C61.1, C63.1, JP32.7, R63.2, U31.1, U31.3, U32.14
VDD_IO16: C65.1, C67.1, JP34.7, R67.2, U33.1, U33.3, U34.14
VDD_IO17: C69.1, C71.1, JP36.7, R71.2, U35.1, U35.3, U36.14
VDD_IO18: C73.1, C75.1, JP38.7, R75.2, U37.1, U37.3, U38.14
VDD_IO19: C77.1, C79.1, JP40.7, R79.2, U39.1, U39.3, U40.14
VDD_IO20: C81.1, C83.1, JP42.7, R83.2, U41.1, U41.3, U42.14
VDD_IO21: C85.1, C87.1, JP44.7, R87.2, U43.1, U43.3, U44.14
VDD_IO22: C89.1, C91.1, JP46.7, R91.2, U45.1, U45.3, U46.14
VDD_IO23: C93.1, C95.1, JP48.7, R95.2, U47.1, U47.3, U48.14
VDD_IO24: C97.1, C99.1, JP50.7, R99.2, U49.1, U49.3, U50.14
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
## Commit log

2015-10-08 Initial design finished
2015-10-08 Added CS pull-up
2015-10-12 Added more notes
2015-10-12 Fixed copy paste error on bypass caps
2015-10-13 Increased size of version font
2015-10-27 Initial code push
2015-11-04 Connected both 3.3V nets
2015-11-23 Incremented to v10
2015-11-24 Increased via sizes and shrunk PCB to exact width of header
2015-11-24 warped a trace
2015-11-25 Renamed a jack to JP and moved over a test point
2016-01-07 updated version number for production
2016-01-08 created panel v10
2016-02-01 added bottom side panel fiducials
2016-02-11 Added LICENSE.md and updated README.md
2016-02-11 removed whitespace
2016-02-25 Changed to actual product photo.
2016-02-25 Added production directory to list of contents.
